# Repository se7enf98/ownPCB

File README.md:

# ownPCB
Own PCB designs with KiCad

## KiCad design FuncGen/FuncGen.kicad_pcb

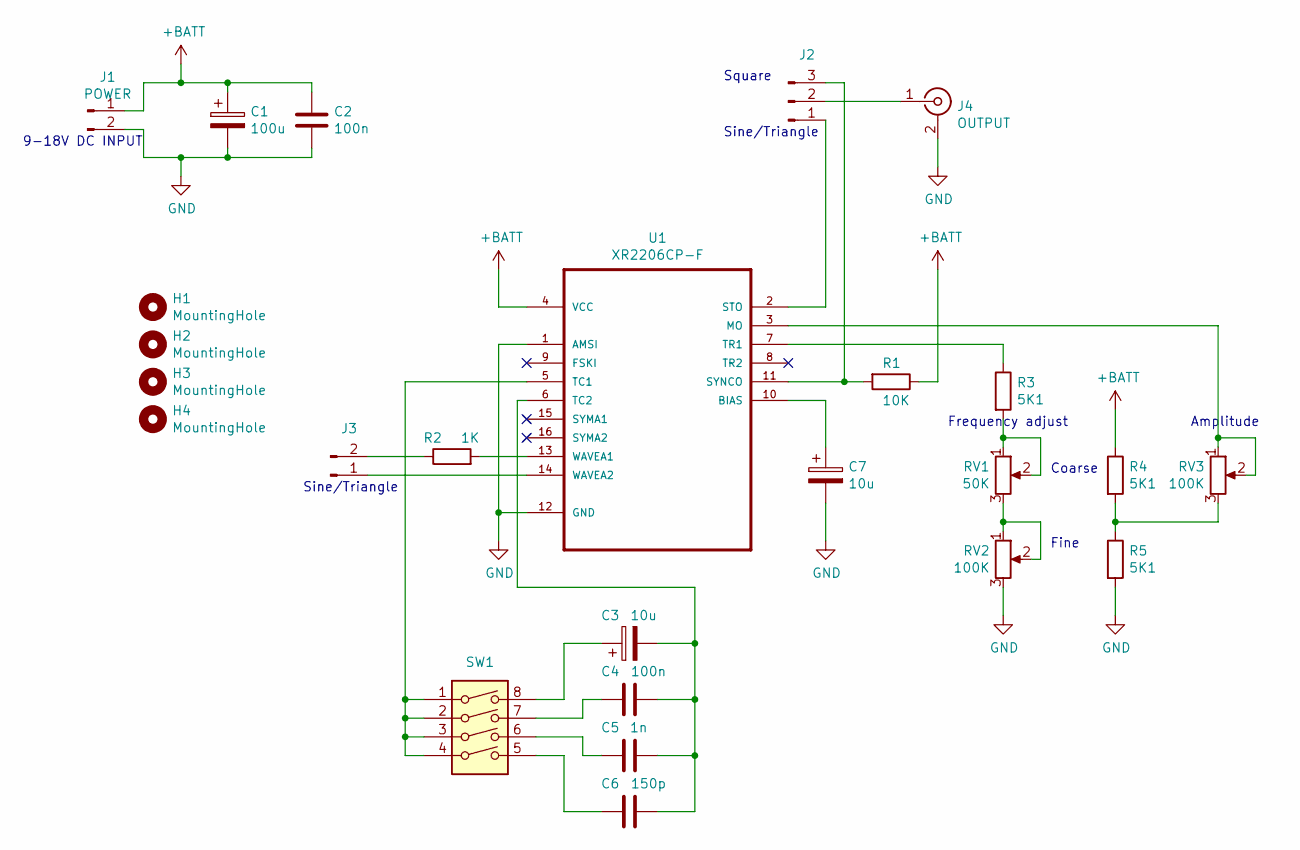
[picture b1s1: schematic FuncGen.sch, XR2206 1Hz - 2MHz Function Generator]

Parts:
C1: 100u; CP_Radial_D8.0mm_P3.50mm
C2, C4: 100n; C_Disc_D6.0mm_W2.5mm_P5.00mm
C3, C7: 10u; CP_Radial_D5.0mm_P2.00mm
C5: 1n; C_Disc_D5.0mm_W2.5mm_P2.50mm
C6: 150p; C_Disc_D5.0mm_W2.5mm_P2.50mm
H1, H2, H3, H4: MountingHole; MountingHole_3mm
J1: POWER; PinHeader_1x02_P2.54mm_Vertical
J2: Conn_01x03_Male; PinHeader_1x03_P2.54mm_Vertical
J3: Conn_01x02_Male; PinHeader_1x02_P2.54mm_Vertical
J4: OUTPUT; rca_yellow
R1: 10K; R_Axial_DIN0207_L6.3mm_D2.5mm_P7.62mm_Horizontal
R2: 1K; R_Axial_DIN0207_L6.3mm_D2.5mm_P7.62mm_Horizontal
R3, R4, R5: 5K1; R_Axial_DIN0207_L6.3mm_D2.5mm_P7.62mm_Horizontal
RV1: 50K; Potentiometer_Piher_T-16H_Single_Horizontal
RV2, RV3: 100K; Potentiometer_Piher_T-16H_Single_Horizontal
SW1: SW_DIP_x04; SW_DIP_SPSTx04_Slide_9.78x12.34mm_W7.62mm_P2.54mm
U1: XR2206CP-F; DIP-16_W7.62mm_Socket

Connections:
+BATT: C1.1, C2.1, J1.1, R1.1, R4.1, U1.4 (VCC)
GND: C1.2, C2.2, C7.2, J1.2, J4.2 (Ext), R5.2, RV2.3, U1.1 (AMSI), U1.12 (GND)
unnamed: C3.1, SW1.8
unnamed: C3.2, C4.2, C5.2, C6.2, U1.6 (TC2)
unnamed: C4.1, SW1.7
unnamed: C5.1, SW1.6
unnamed: C6.1, SW1.5
unnamed: C7.1, U1.10 (BIAS)
unnamed: J2.1, U1.2 (STO)
unnamed: J2.2, J4.1 (In)
unnamed: J2.3, R1.2, U1.11 (SYNCO)
unnamed: J3.1, U1.14 (WAVEA2)
unnamed: J3.2, R2.1
unnamed: R2.2, U1.13 (WAVEA1)
unnamed: R3.1, U1.7 (TR1)
unnamed: R3.2, RV1.1, RV1.2
unnamed: R4.2, R5.1, RV3.3
unnamed: RV1.3, RV2.1, RV2.2
unnamed: RV3.1, RV3.2, U1.3 (MO)
unnamed: SW1.1, SW1.2, SW1.3, SW1.4, U1.5 (TC1)

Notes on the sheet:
Coarse
Fine
Frequency adjust
Amplitude
9-18V DC INPUT
Square
Sine/Triangle

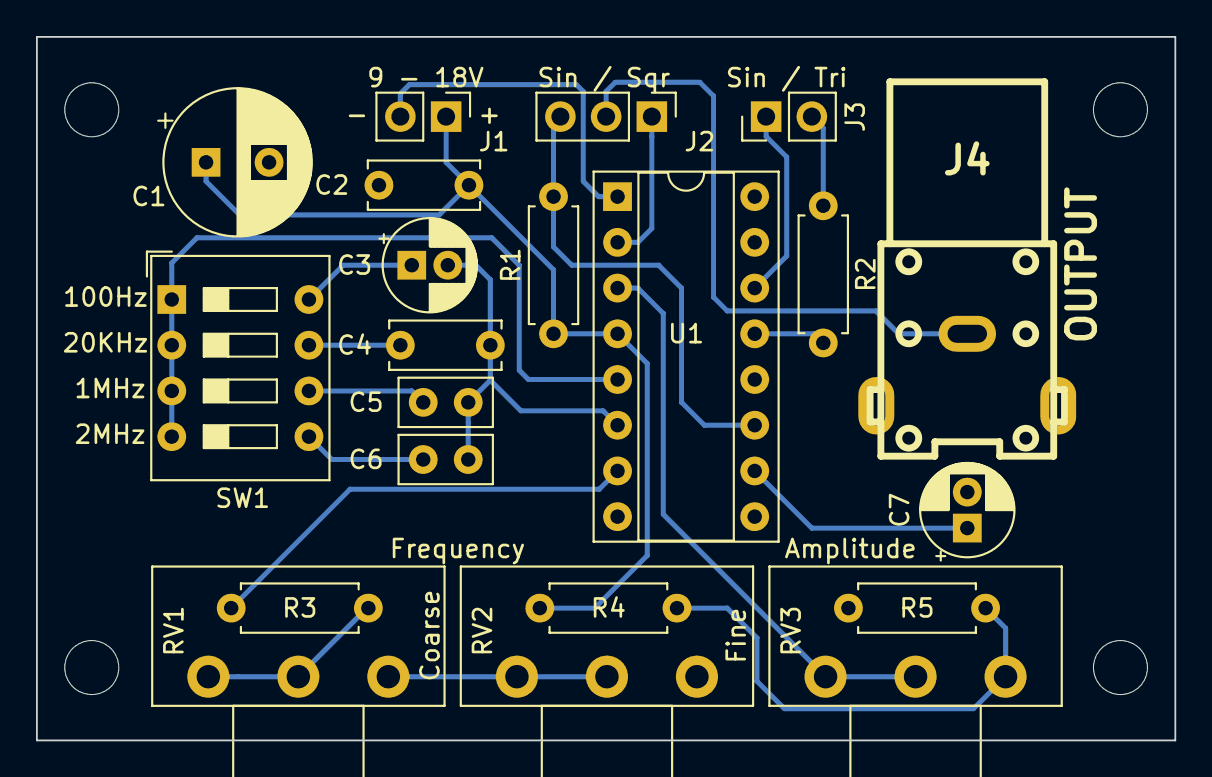
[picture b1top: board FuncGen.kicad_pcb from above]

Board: 2 copper layers, 63.2 x 39.1 mm, 25 parts (0 on the bottom side), 20 nets.

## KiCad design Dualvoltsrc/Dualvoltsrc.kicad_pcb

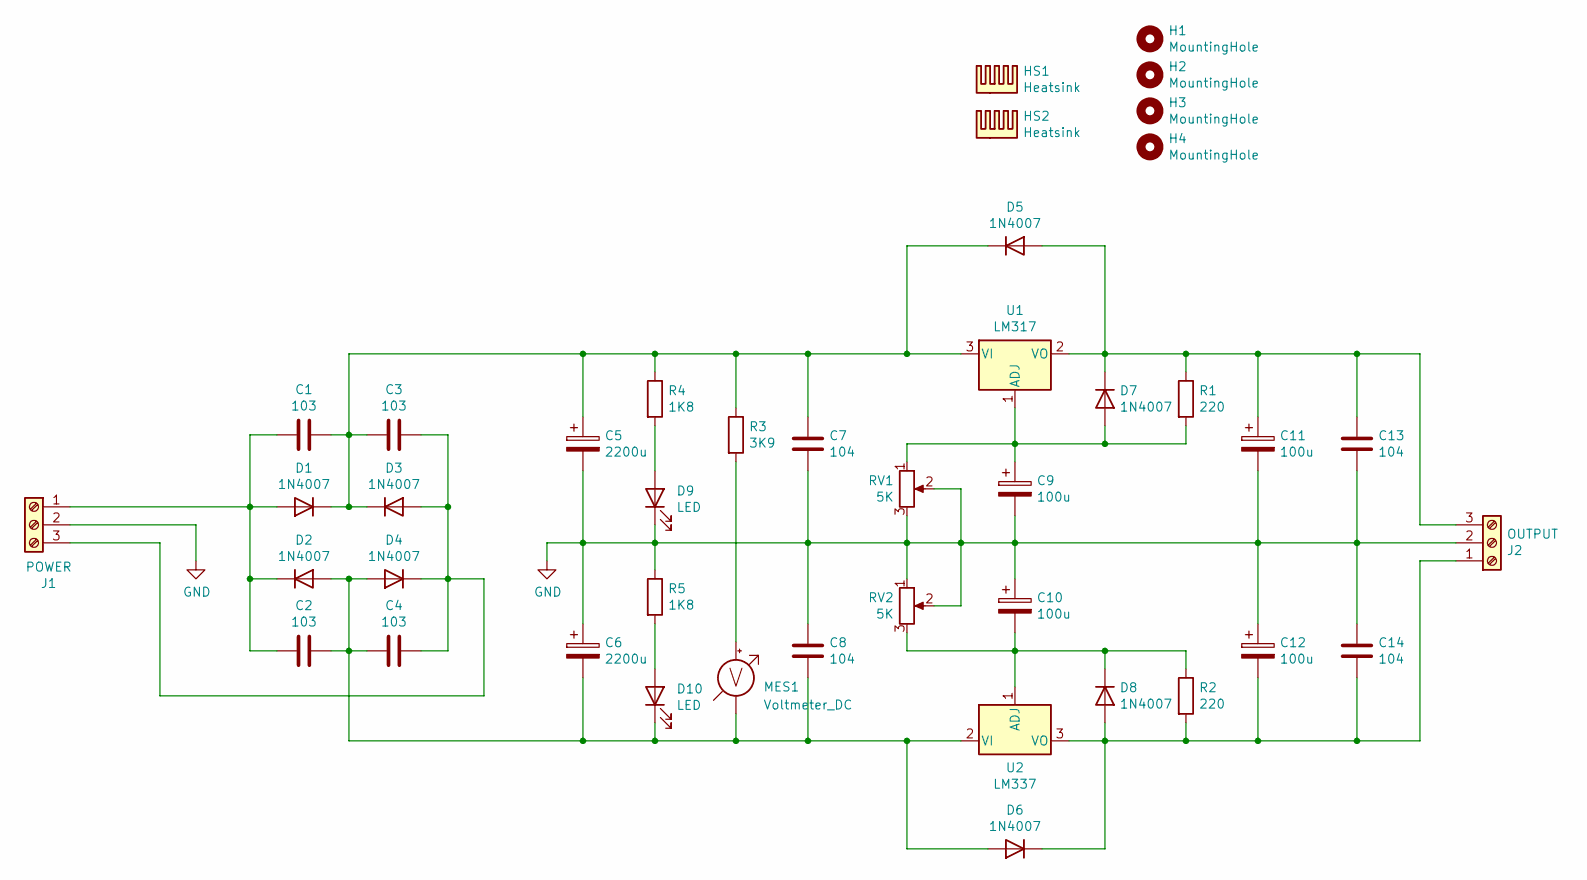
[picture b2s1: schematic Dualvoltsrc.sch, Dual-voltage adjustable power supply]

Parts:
C1, C2, C3, C4: 103; C_Disc_D6.0mm_W4.4mm_P5.00mm
C5, C6: 2200u; CP_Radial_D18.0mm_P7.50mm
C7, C8, C13, C14: 104; C_Disc_D6.0mm_W2.5mm_P5.00mm
C9, C10, C11, C12: 100u; CP_Radial_D6.3mm_P2.50mm
D1, D2, D3, D4, D5, D6, D7, D8: 1N4007; D_DO-41_SOD81_P10.16mm_Horizontal
D9, D10: LED; LED_D3.0mm
H1, H2, H3, H4: MountingHole; MountingHole_3mm
HS1, HS2: Heatsink; Heatsink_Fischer_SK104-STC-STIC_35x13mm_2xDrill2.5mm
J1: POWER; TerminalBlock_Phoenix_MKDS-1,5-3-5.08_1x03_P5.08mm_Horizont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
J2: OUTPUT; TerminalBlock_Phoenix_MKDS-1,5-3-5.08_1x03_P5.08mm_Horizont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
MES1: Voltmeter_DC; PinSocket_1x02_P2.54mm_Vertical
R1, R2: 220; R_Axial_DIN0207_L6.3mm_D2.5mm_P10.16mm_Horizontal
R3: 3K9; R_Axial_DIN0207_L6.3mm_D2.5mm_P10.16mm_Horizontal
R4, R5: 1K8; R_Axial_DIN0207_L6.3mm_D2.5mm_P10.16mm_Horizontal
RV1, RV2: 5K; PinSocket_1x03_P2.54mm_Vertical
U1: LM317; TO-220-3_Vertical
U2: LM337; TO-220-3_Vertical

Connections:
GND: C5.2, C6.1, C7.2, C8.1, C9.2, C10.1, C11.2, C12.1, C13.2, C14.1, D9.1 (K), J1.2, J2.2, R5.1, RV1.2, RV1.3, RV2.1, RV2.2
unnamed: C1.1, C3.2, C5.1, C7.1, D1.1 (K), D3.1 (K), D5.1 (K), R3.1, R4.1, U1.3 (VI)
unnamed: C1.2, C2.2, D1.2 (A), D2.1 (K), J1.1
unnamed: C2.1, C4.2, C6.2, C8.2, D2.2 (A), D4.2 (A), D6.2 (A), D10.1 (K), MES1.1 (-), U2.2 (VI)
unnamed: C3.1, C4.1, D3.2 (A), D4.1 (K), J1.3
unnamed: C9.1, D7.2 (A), R1.2, RV1.1, U1.1 (ADJ)
unnamed: C10.2, D8.1 (K), R2.1, RV2.3, U2.1 (ADJ)
unnamed: C11.1, C13.1, D5.2 (A), D7.1 (K), J2.3, R1.1, U1.2 (VO)
unnamed: C12.2, C14.2, D6.1 (K), D8.2 (A), J2.1, R2.2, U2.3 (VO)
unnamed: D9.2 (A), R4.2
unnamed: D10.2 (A), R5.2
unnamed: MES1.2 (+), R3.2

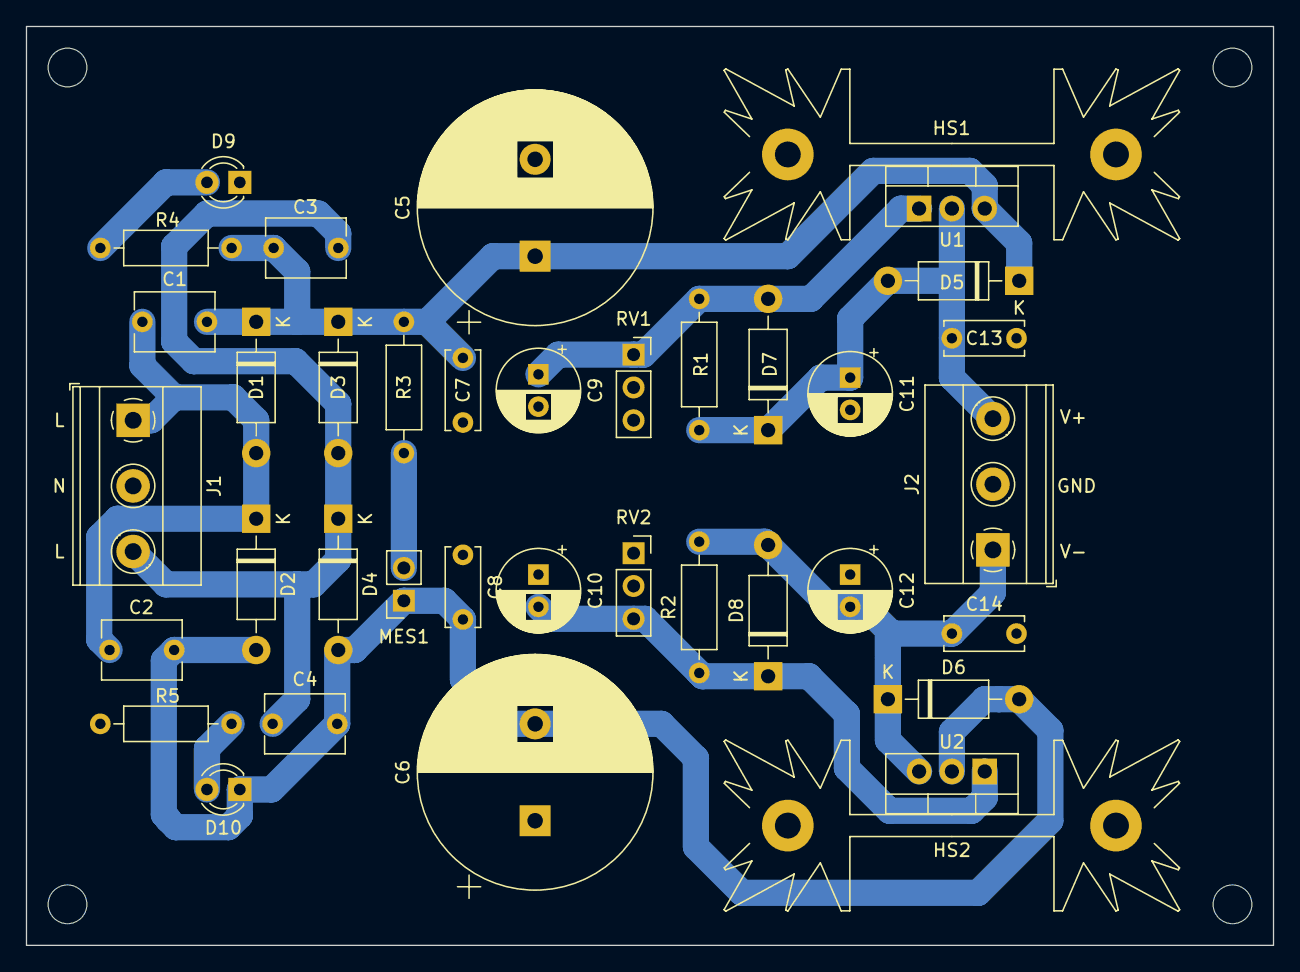
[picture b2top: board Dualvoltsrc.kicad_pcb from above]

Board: 2 copper layers, 96.5 x 71.1 mm, 42 parts (0 on the bottom side), 12 nets.

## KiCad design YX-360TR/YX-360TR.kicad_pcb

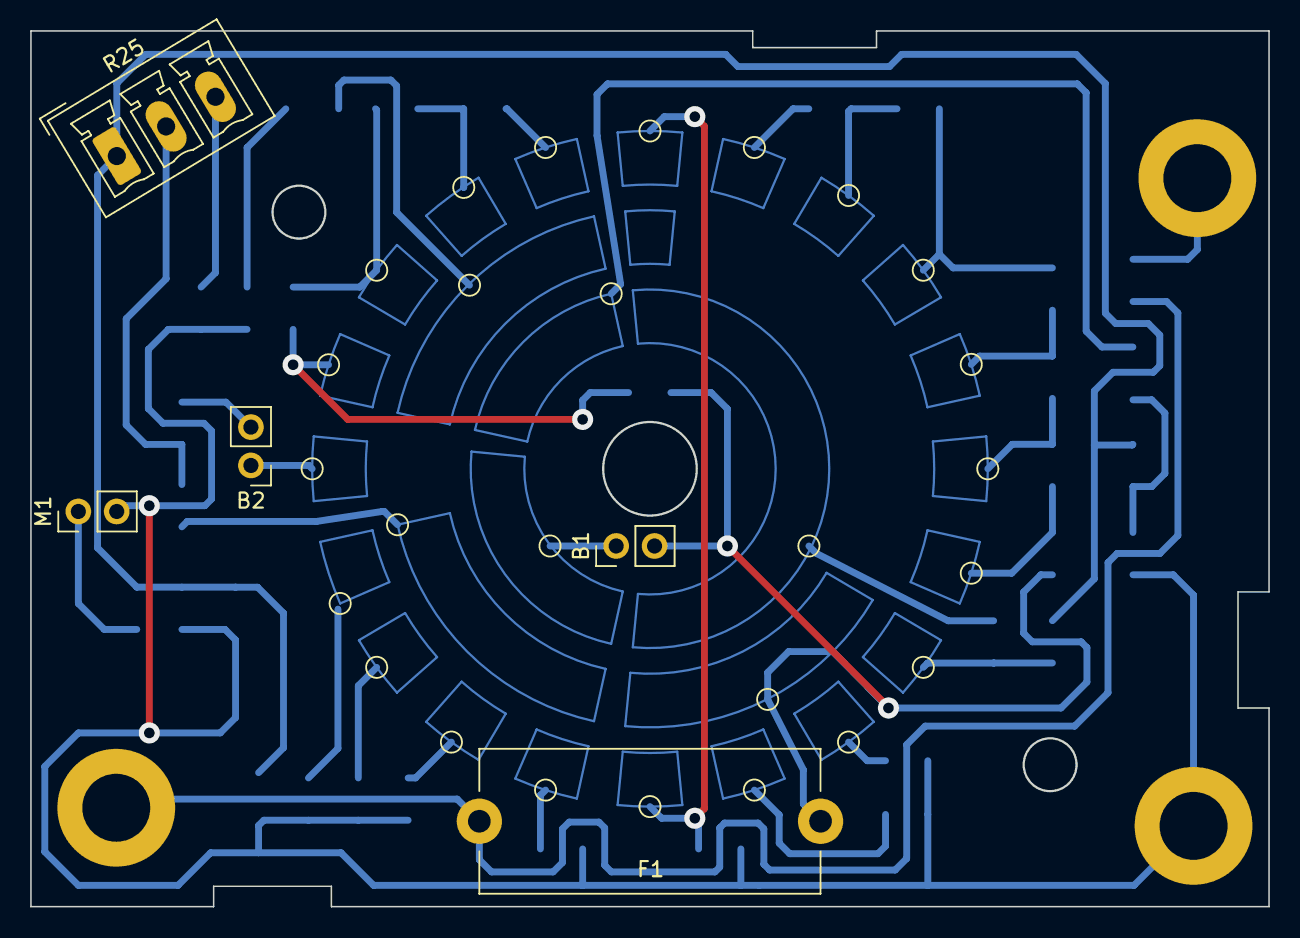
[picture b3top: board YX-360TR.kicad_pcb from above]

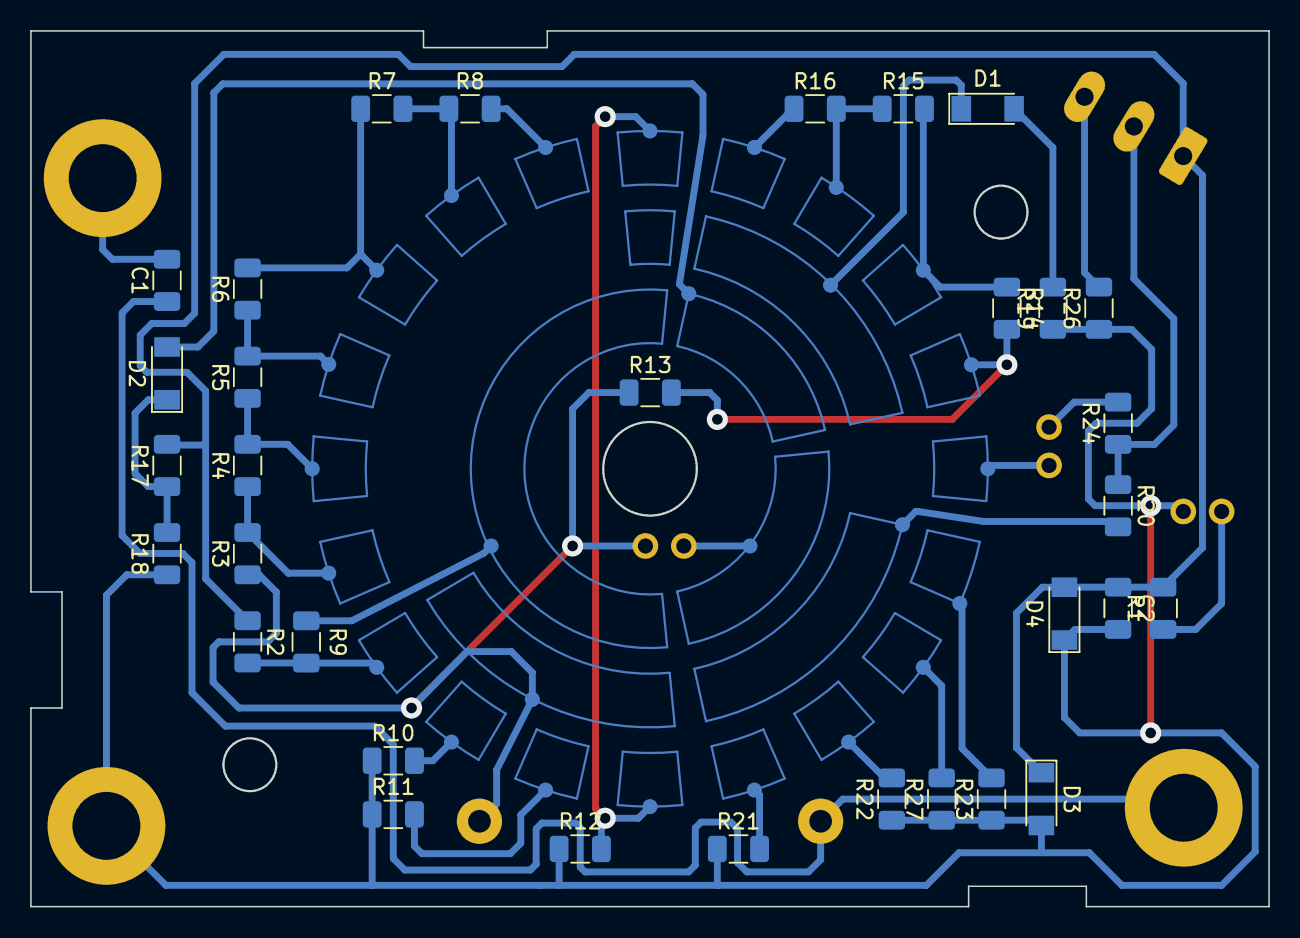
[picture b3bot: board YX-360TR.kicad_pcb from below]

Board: 2 copper layers, 82.0 x 58.0 mm, 66 parts (32 on the bottom side), 35 nets.

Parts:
B1: 1.5Vx2; PinHeader_1x02_P2.54mm_Vertical
B2: 9V; PinHeader_1x02_P2.54mm_Vertical
C1, C2: 0.047u; C_1206_3216Metric
D1, D2, D3, D4: 1N4148; D_MiniMELF
F1: 250V/0.5A; Fuseholder_Cylinder-5x20mm_Stelvio-Kontek_PTF78_Horizontal_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
M1: 44uA/2K; PinHeader_1x02_P2.54mm_Vertical
R1: 1.2K; R_1206_3216Metric
R2: 240R; R_1206_3216Metric
R3: 5K; R_1206_3216Metric
R4: 40K; R_1206_3216Metric
R5: 150K; R_1206_3216Metric
R6: 800K; R_1206_3216Metric
R7: 4M; R_1206_3216Metric
R8: 15M; R_1206_3216Metric
R9: 3K; R_1206_3216Metric
R10: 92R; R_1206_3216Metric
R11: 9R; R_1206_3216Metric
R12: 1R; R_1206_3216Metric
R13: 74K; R_1206_3216Metric
R14: 320K; R_1206_3216Metric
R15: 1.6M; R_1206_3216Metric
R16: 6M; R_1206_3216Metric
R17, R19: 2K; R_1206_3216Metric
R18: 41K; R_1206_3216Metric
R20: 44K; R_1206_3216Metric
R21: 19R; R_1206_3216Metric
R22: 200R; R_1206_3216Metric
R23: 33.3K; R_1206_3216Metric
R24: 194K; R_1206_3216Metric
R25: 10K; PhoenixContact_MCV_1,5_3-G-3.81_1x03_P3.81mm_Vertical
R26: 16K; R_1206_3216Metric
R27: 2.08K; R_1206_3216Metric
TP1, TP21: 1000; TestPoint_Pad_D1.0mm
TP2, TP11, TP20: 250; TestPoint_Pad_D1.0mm
TP3, TP19: 50; TestPoint_Pad_D1.0mm
TP4, TP18: 10; TestPoint_Pad_D1.0mm
TP5, TP9: 2.5; TestPoint_Pad_D1.0mm
TP6: 0.5; TestPoint_Pad_D1.0mm
TP7: A; TestPoint_Pad_D1.0mm
TP8: 100uA; TestPoint_Pad_D1.0mm
TP10: 25; TestPoint_Pad_D1.0mm
TP12: OFF; TestPoint_Pad_D1.0mm
TP13: x1; TestPoint_Pad_D1.0mm
TP14: x10; TestPoint_Pad_D1.0mm
TP15: x100; TestPoint_Pad_D1.0mm
TP16: x1K; TestPoint_Pad_D1.0mm
TP17: x10K; TestPoint_Pad_D1.0mm
TP22: B; TestPoint_Pad_D1.0mm
TP23: +; MountingHole_4.5mm_Pad
TP24: OUTPUT; MountingHole_4.5mm_Pad
TP25: -COM; MountingHole_4.5mm_Pad
TP26: C; TestPoint_Pad_D1.0mm
TP27: D; TestPoint_Pad_D1.0mm
TP28: E; TestPoint_Pad_D1.0mm
TP29: F; TestPoint_Pad_D1.0mm

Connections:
/OFF: R12.2, TP11.1, TP12.1
unnamed: B1.1, TP27.1
unnamed: B1.2, F1.1, R3.1, R13.1, TP22.1
unnamed: B2.1, TP17.1
unnamed: B2.2, R24.2
unnamed: C1.1, F1.2, TP23.1
unnamed: C1.2, TP24.1
unnamed: C2.1, D3.1, D4.2, R1.2, R2.1, R17.2, R25.1
unnamed: C2.2, D3.2, D4.1, M1.2, R10.1, R11.1, R12.1, R18.1, R19.1, R21.1, R22.1, R23.1, R26.1, R27.1, TP25.1
unnamed: D1.1, TP29.1
unnamed: D1.2, R19.2
unnamed: D2.1, R17.1, R18.2
unnamed: D2.2, TP28.1
unnamed: M1.1, R1.1
unnamed: R2.2, R9.1, TP8.1
unnamed: R3.2, R4.1, TP6.1
unnamed: R4.2, R5.1, TP5.1
unnamed: R5.2, R6.1, TP4.1
unnamed: R6.2, R7.1, TP3.1
unnamed: R7.2, R8.1, TP2.1
unnamed: R8.2, TP1.1
unnamed: R9.2, TP7.1
unnamed: R10.2, TP9.1
unnamed: R11.2, TP10.1
unnamed: R13.2, R14.2, TP18.1
unnamed: R14.1, R15.2, TP19.1
unnamed: R15.1, R16.2, TP20.1
unnamed: R16.1, TP21.1
unnamed: R20.1, R24.1, R25.2
unnamed: R20.2, TP26.1
unnamed: R21.2, TP13.1
unnamed: R22.2, TP14.1
unnamed: R23.2, TP16.1
unnamed: R25.3, R26.2
unnamed: R27.2, TP15.1

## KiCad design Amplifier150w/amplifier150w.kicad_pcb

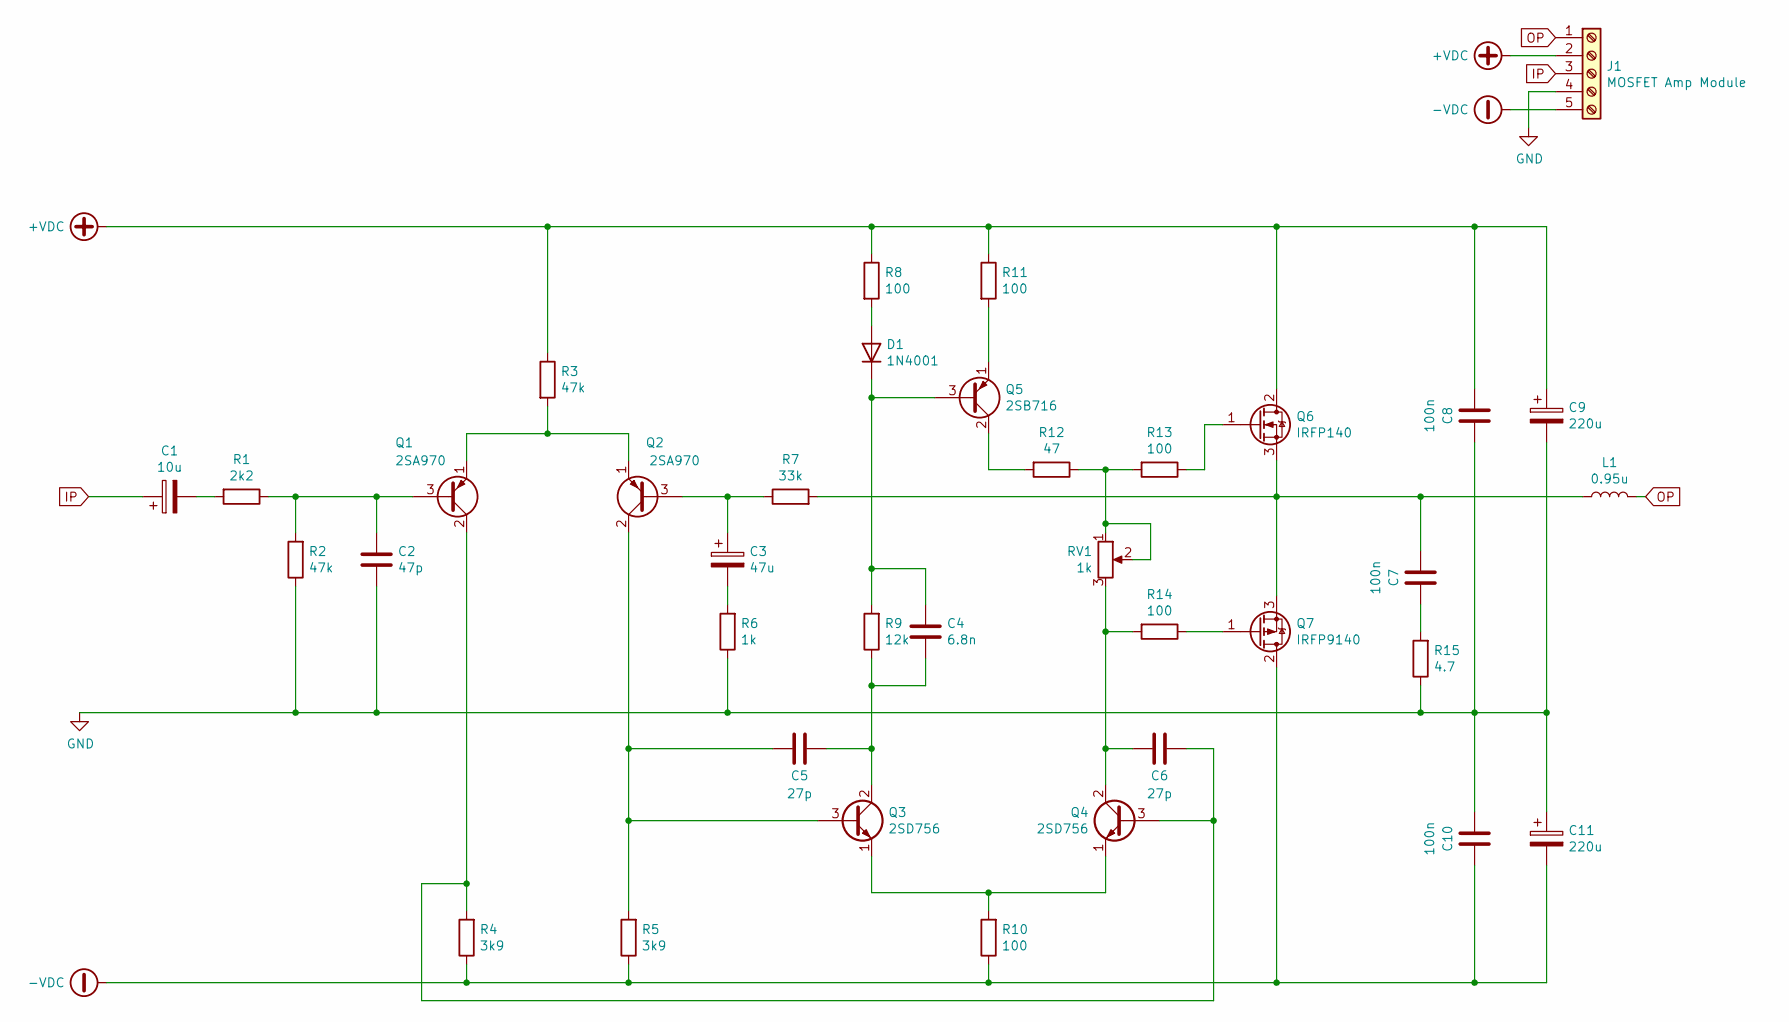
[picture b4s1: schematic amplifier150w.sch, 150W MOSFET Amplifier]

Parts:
C1: 10u; CP_Radial_D5.0mm_P2.00mm
C2: 47p; C_Disc_D5.0mm_W2.5mm_P5.00mm
C3: 47u; CP_Radial_D6.3mm_P2.50mm
C4: 6.8n; C_Rect_L7.0mm_W3.5mm_P5.00mm
C5, C6: 27p; C_Disc_D5.0mm_W2.5mm_P5.00mm
C7, C8, C10: 100n; C_Rect_L10.0mm_W4.0mm_P7.50mm_MKS4
C9, C11: 220u; CP_Radial_D10.0mm_P5.00mm
D1: 1N4001; D_DO-41_SOD81_P10.16mm_Horizontal
J1: MOSFET Amp Module; Altech_AK300_1x05_P5.00mm_45-Degree
L1: 0.95u; L_Axial_L16.0mm_D7.5mm_P20.32mm_Horizontal_Fastron_XHBCC
Q1, Q2: 2SA970; TO-92
Q3, Q4: 2SD756; TO-92
Q5: 2SB716; TO-92
Q6: IRFP140; TO-247-3_Vertical
Q7: IRFP9140; TO-247-3_Vertical
R1: 2k2; R_Axial_DIN0207_L6.3mm_D2.5mm_P10.16mm_Horizontal
R2, R3: 47k; R_Axial_DIN0207_L6.3mm_D2.5mm_P10.16mm_Horizontal
R4, R5: 3k9; R_Axial_DIN0207_L6.3mm_D2.5mm_P10.16mm_Horizontal
R6: 1k; R_Axial_DIN0207_L6.3mm_D2.5mm_P10.16mm_Horizontal
R7: 33k; R_Axial_DIN0207_L6.3mm_D2.5mm_P10.16mm_Horizontal
R8, R10, R11, R13, R14: 100; R_Axial_DIN0207_L6.3mm_D2.5mm_P10.16mm_Horizontal
R9: 12k; R_Axial_DIN0414_L11.9mm_D4.5mm_P15.24mm_Horizontal
R12: 47; R_Axial_DIN0207_L6.3mm_D2.5mm_P10.16mm_Horizontal
R15: 4.7; R_Axial_Power_L20.0mm_W6.4mm_P25.40mm
RV1: 1k; Potentiometer_Bourns_3386P_Vertical

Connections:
+VDC: C8.2, C9.1, J1.2, Q6.2 (D), R3.1, R8.1, R11.1
-VDC: C10.1, C11.2, J1.5, Q7.2 (D), R4.1, R5.1, R10.1
GND: C2.2, C8.1, C9.2, C10.2, C11.1, J1.4, R2.1, R6.1, R15.1
IP: C1.1, J1.3
unnamed: C1.2, R1.2
unnamed: C2.1, Q1.3 (B), R1.1, R2.2
unnamed: C3.1, Q2.3 (B), R7.1
unnamed: C3.2, R6.2
unnamed: C4.1, D1.1 (K), Q5.3 (B), R9.2
unnamed: C4.2, C5.1, Q3.2 (C), R9.1
unnamed: C5.2, Q2.2 (C), Q3.3 (B), R5.2
unnamed: C6.1, Q1.2 (C), Q4.3 (B), R4.2
unnamed: C6.2, Q4.2 (C), R14.2, RV1.3
unnamed: C7.1, R15.2
unnamed: C7.2, L1.1, Q6.3 (S), Q7.3 (S), R7.2
unnamed: D1.2 (A), R8.2
unnamed: Q1.1 (E), Q2.1 (E), R3.2
unnamed: Q3.1 (E), Q4.1 (E), R10.2
unnamed: Q5.1 (E), R11.2
unnamed: Q5.2 (C), R12.2
unnamed: Q6.1 (G), R13.1
unnamed: Q7.1 (G), R14.1
unnamed: R12.1, R13.2, RV1.1, RV1.2
OP: J1.1, L1.2

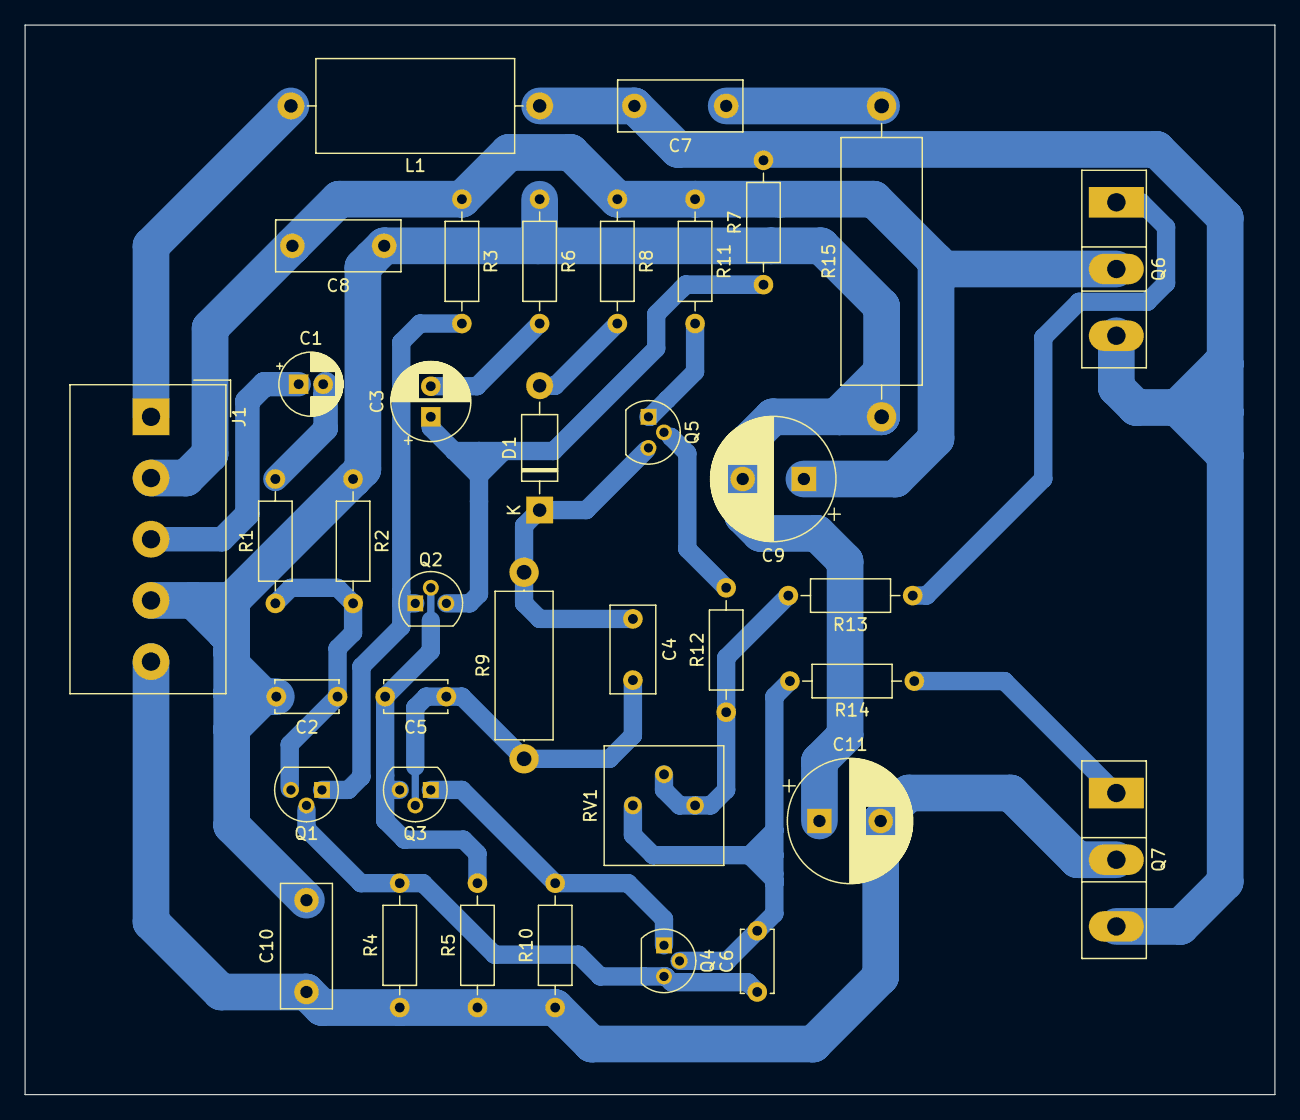
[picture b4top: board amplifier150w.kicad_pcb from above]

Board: 2 copper layers, 102.1 x 87.4 mm, 37 parts (0 on the bottom side), 24 nets.

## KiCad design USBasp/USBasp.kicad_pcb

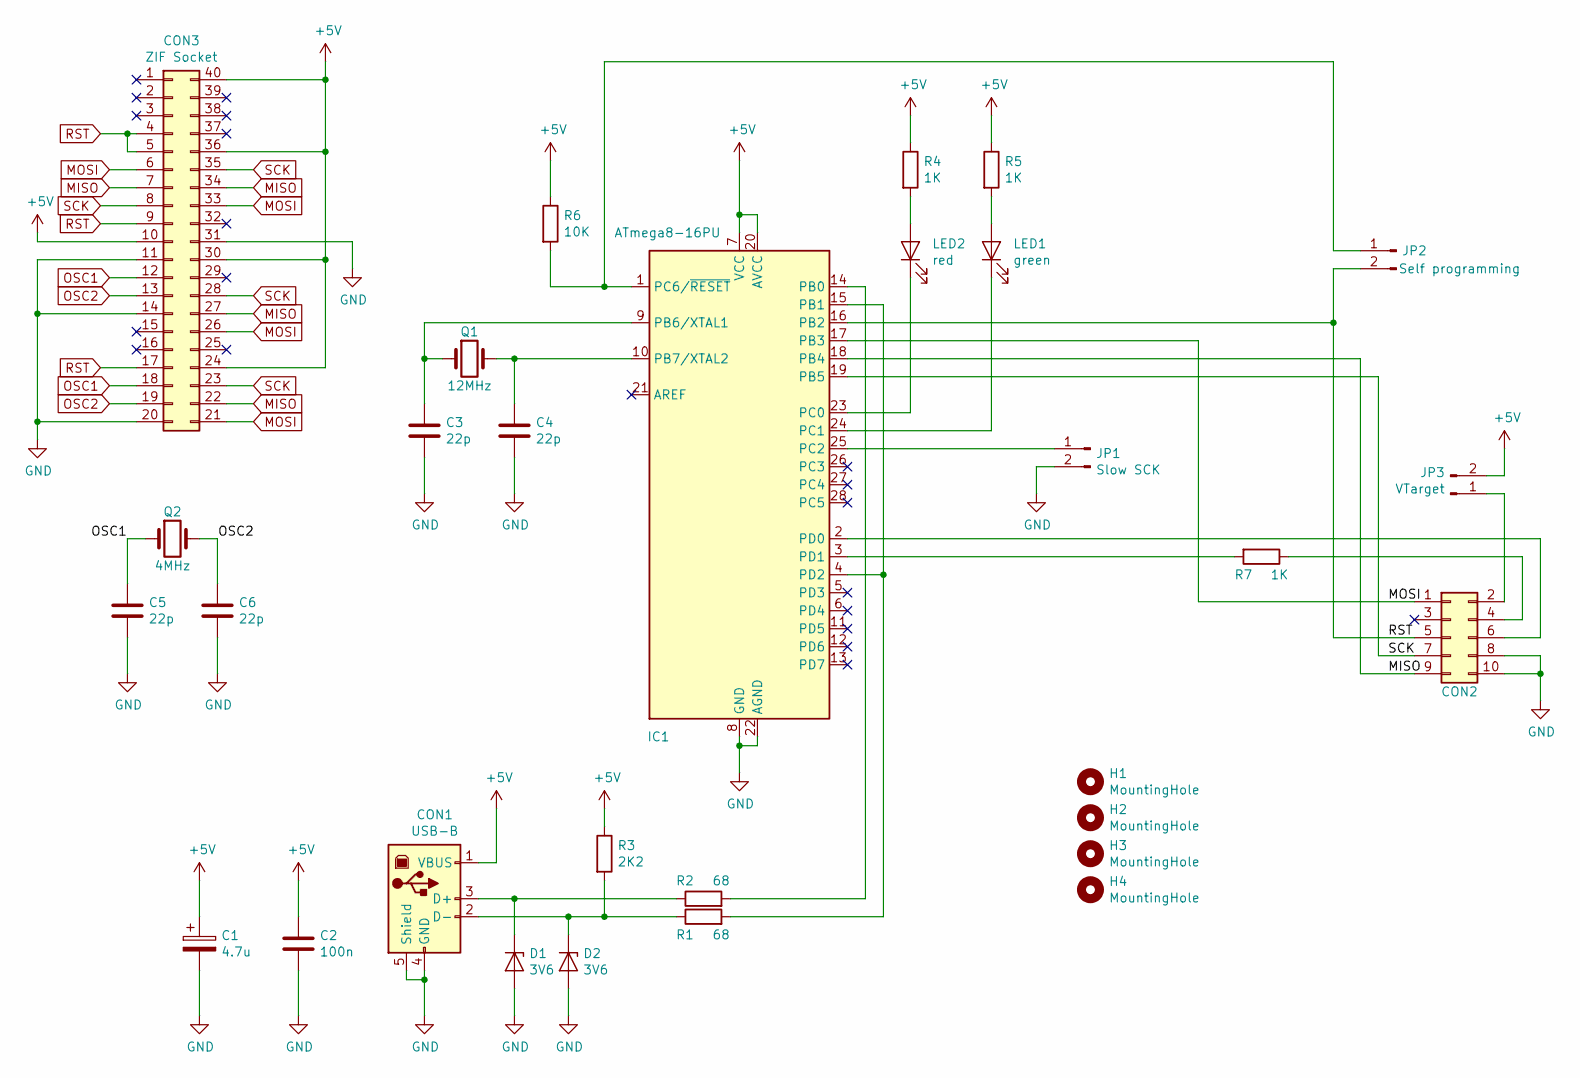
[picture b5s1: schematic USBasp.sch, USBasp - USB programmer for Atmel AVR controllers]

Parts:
C1: 4.7u; CP_Radial_D4.0mm_P1.50mm
C2: 100n; C_Disc_D6.0mm_W2.5mm_P5.00mm
C3, C4, C5, C6: 22p; C_Disc_D5.0mm_W2.5mm_P2.50mm
CON1: USB-B; USB_B_OST_USB-B1HSxx_Horizontal
CON2: ICSP; vasch_strip_5x2
CON3: ZIF Socket; 3M_Textool_240-1288-00-0602J_2x20_P2.54mm
D1, D2: 3V6; D_DO-35_SOD27_P7.62mm_Horizontal
H1, H2, H3, H4: MountingHole; MountingHole_3mm
IC1: ATmega8-16PU; DIP-28_W7.62mm_Socket
JP1: Slow SCK; PinHeader_1x02_P2.54mm_Vertical
JP2: Self programming; PinHeader_1x02_P2.54mm_Vertical
JP3: VTarget; PinHeader_1x02_P2.54mm_Vertical
LED1: green; LED_D3.0mm
LED2: red; LED_D3.0mm
Q1: 12MHz; Crystal_HC49-U_Vertical
Q2: 4MHz; Crystal_HC49-4H_Vertical
R1, R2: 68; R_Axial_DIN0207_L6.3mm_D2.5mm_P7.62mm_Horizontal
R3: 2K2; R_Axial_DIN0207_L6.3mm_D2.5mm_P7.62mm_Horizontal
R4, R5, R7: 1K; R_Axial_DIN0207_L6.3mm_D2.5mm_P7.62mm_Horizontal
R6: 10K; R_Axial_DIN0207_L6.3mm_D2.5mm_P7.62mm_Horizontal

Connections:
+5V: C1.1, C2.1, CON1.1 (VBUS), CON3.10, CON3.24, CON3.30, CON3.36, CON3.40, IC1.7 (VCC), IC1.20 (AVCC), JP3.2, R3.1, R4.1, R5.1, R6.1
GND: C1.2, C2.2, C3.2, C4.2, C5.2, C6.2, CON1.4 (GND), CON1.5 (Shield), CON2.8, CON2.10, CON3.11, CON3.14, CON3.20, CON3.31, D1.2 (A), D2.2 (A), IC1.8 (GND), IC1.22 (AGND), JP1.2
MISO: CON2.9, CON3.7, CON3.22, CON3.27, CON3.34, IC1.18 (PB4)
MOSI: CON2.1, CON3.6, CON3.21, CON3.26, CON3.33, IC1.17 (PB3)
unnamed: C3.1, IC1.9 (PB6/XTAL1), Q1.1
unnamed: C4.1, IC1.10 (PB7/XTAL2), Q1.2
unnamed: CON1.2 (D-), D2.1 (K), R1.1, R3.2
unnamed: CON1.3 (D+), D1.1 (K), R2.1
unnamed: CON2.2, JP3.1
unnamed: CON2.4, R7.1
unnamed: CON2.6, IC1.2 (PD0)
unnamed: IC1.1 (PC6/~RESET), JP2.1, R6.2
unnamed: IC1.3 (PD1), R7.2
unnamed: IC1.14 (PB0), R2.2
unnamed: IC1.4 (PD2), IC1.15 (PB1), R1.2
unnamed: IC1.23 (PC0), LED2.1 (K)
unnamed: IC1.24 (PC1), LED1.1 (K)
unnamed: IC1.25 (PC2), JP1.1
unnamed: LED1.2 (A), R5.2
unnamed: LED2.2 (A), R4.2
OSC1: C5.1, CON3.12, CON3.18, Q2.1
OSC2: C6.1, CON3.13, CON3.19, Q2.2
RST: CON2.5, CON3.4, CON3.5, CON3.9, CON3.17, IC1.16 (PB2), JP2.2
SCK: CON2.7, CON3.8, CON3.23, CON3.28, CON3.35, IC1.19 (PB5)

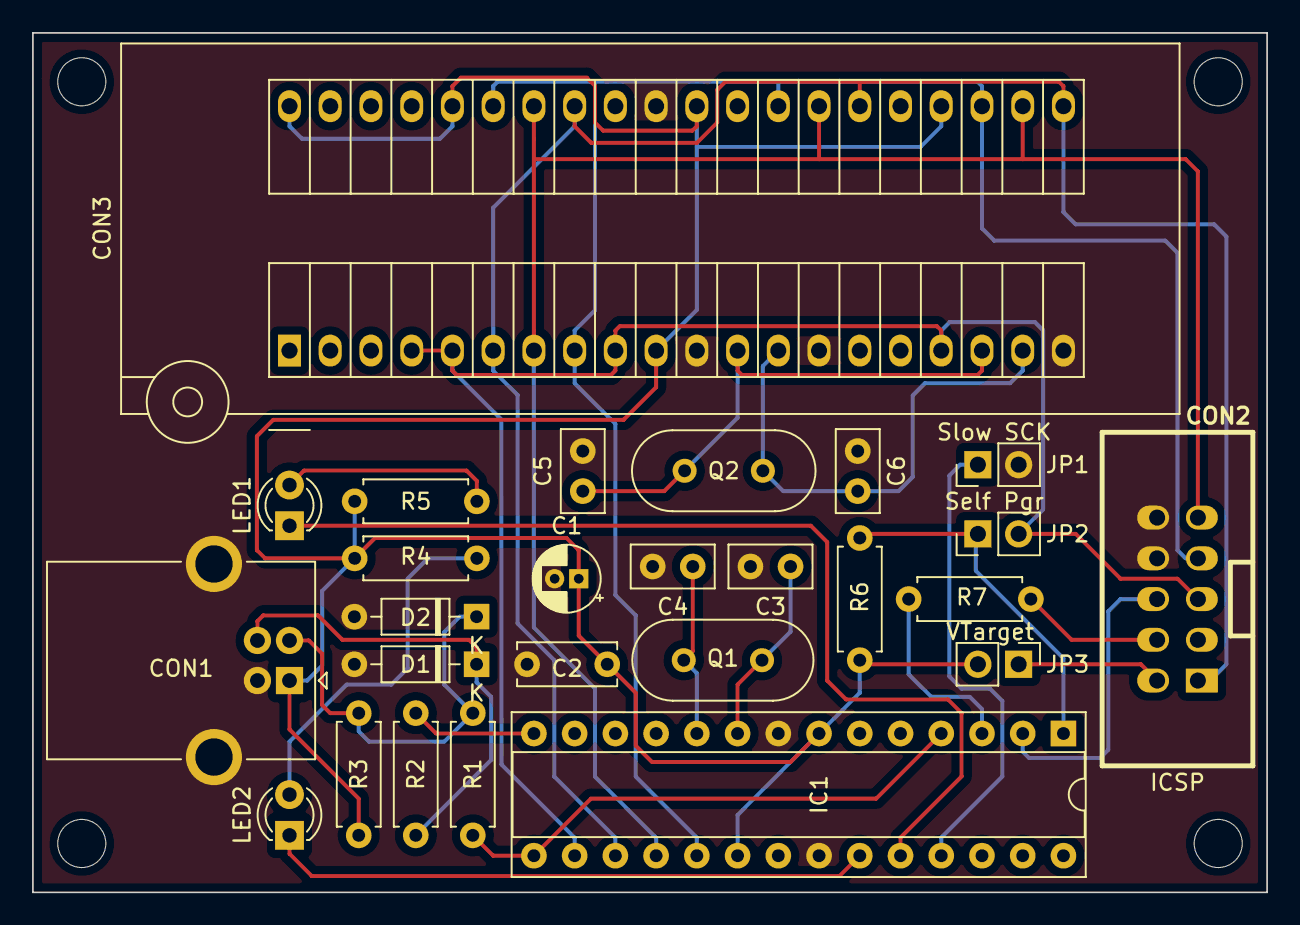
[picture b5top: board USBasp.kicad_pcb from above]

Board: 2 copper layers, 77.0 x 53.6 mm, 30 parts (0 on the bottom side), 24 nets.

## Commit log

2020-04-01 Create LICENSE

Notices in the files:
Amplifier150w/amplifier150w.sch:
creativecommons.org/licenses/by/4.0
License: CC BY 4.0
